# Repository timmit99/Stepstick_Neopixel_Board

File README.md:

# Stepstick Neopixel Board
Dual output level shifted Stepstick adaptor for neopixel strips.

## Overview
This board converts the logic level `STEP` and `DIR` outputs on a Stepstick header to 5V level for properly driving 2 Neopixel strips. Input 5V from a 2-pin JST-XH header, with 2 outputs on 3-pin JST-XH headers.

### Setup
To use, simply configure the `STEP`/`DIR` pin for the socket you plug the board into as your neopixel pin. It's that simple!

## BOM

|  Reference  |        Name          |             Note              |  Quantity |  LCSC   |
|    :---:    |        :---:         |            :---:              |   :---:   |  :---:  |
| J3, J4      |      Strip Out       |      3-pin JST HX, B3B-XH     |     2     | C144394 |
| J5          |       5V In          |      2-pin JST HX, B2B-XH     |     1     | C495685 |
| U1, U2      |     Level Shifter    |      74LVC1G17GV (SOT753)     |     2     |  C6076  |
| U3          |   Stepstick Header   | 8-pin Male Header Pin, 2.54mm |     2     | C124381 |

### [Interactive bom](http://htmlpreview.github.io/?https://github.com/timmit99/Stepstick_Neopixel_Board/blob/main/iBOM/StepstickPixel.html)

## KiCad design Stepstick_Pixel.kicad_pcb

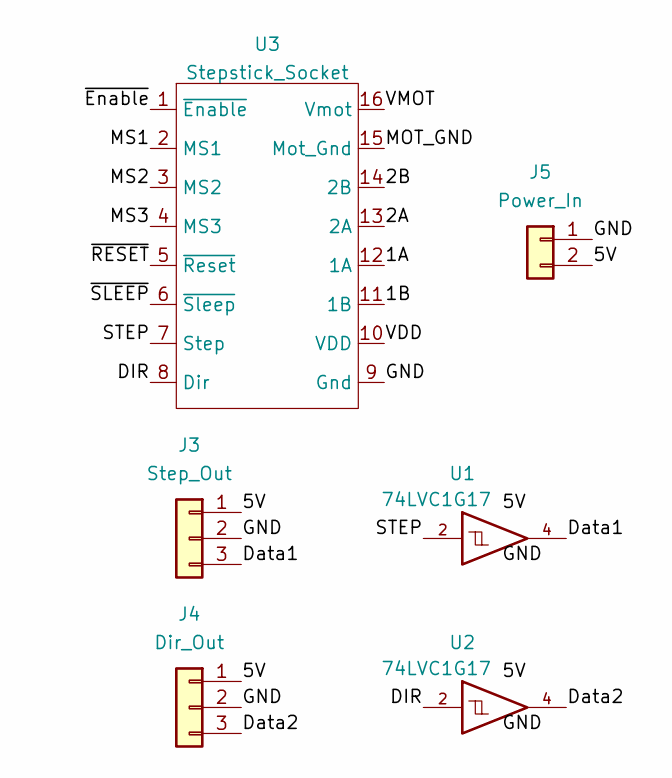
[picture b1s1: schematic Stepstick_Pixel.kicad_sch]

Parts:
J3: Step_Out; JST_XH_B3B-XH-A_1x03_P2.50mm_Vertical
J4: Dir_Out; JST_XH_B3B-XH-A_1x03_P2.50mm_Vertical
J5: Power_In; JST_XH_B2B-XH-A_1x02_P2.50mm_Vertical
U1, U2: 74LVC1G17; SOT-753
U3: Stepstick_Socket

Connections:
/1A: U3.12 (1A)
/1B: U3.11 (1B)
/2A: U3.13 (2A)
/2B: U3.14 (2B)
/DIR: U2.2, U3.8 (Dir)
/Data1: J3.3, U1.4
/Data2: J4.3, U2.4
/MOT_GND: U3.15 (Mot_Gnd)
/MS1: U3.2 (MS1)
/MS2: U3.3 (MS2)
/MS3: U3.4 (MS3)
/STEP: U1.2, U3.7 (Step)
/VDD: U3.10 (VDD)
/VMOT: U3.16 (Vmot)
/~Enable: U3.1 (~Enable)
/~RESET: U3.5 (~Reset)
/~SLEEP: U3.6 (~Sleep)
GND: J3.2, J4.2, J5.1, U1.3 (GND), U2.3 (GND), U3.9 (Gnd)
VCC: J3.1, J4.1, J5.2, U1.5 (VCC), U2.5 (VCC)

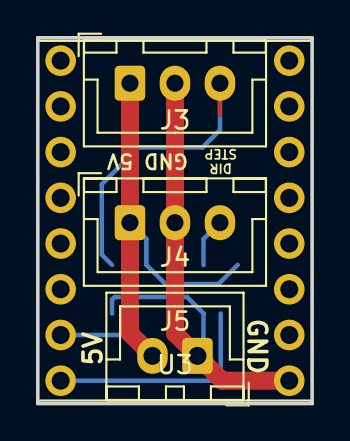
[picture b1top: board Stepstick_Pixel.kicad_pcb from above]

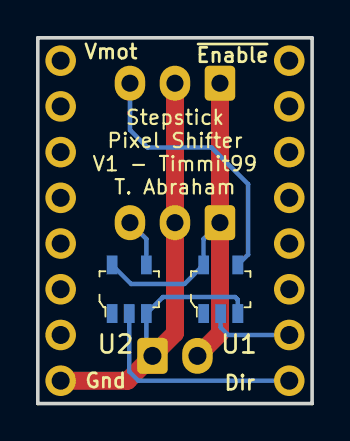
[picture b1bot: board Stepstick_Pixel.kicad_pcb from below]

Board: 2 copper layers, 15.2 x 20.3 mm, 6 parts (2 on the bottom side), 6 nets.

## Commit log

2022-12-16 Initial Commit
    Initial release of the Stepstick Neopixel Board
    Board designed to level shift the STEP and DIR pins of a standard stepper driver socket to 5V for use with 2 neopixel strips.
2022-12-16 Add README
2022-12-16 README Update
2022-12-16 Update README.md
    Add BOM and links
2022-12-16 Update README.md
    Add "setup instructions"
